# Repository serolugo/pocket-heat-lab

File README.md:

# Pocket Heat Lab

## 📌 Overview
**Pocket Heat Lab** is a compact thermal control laboratory designed to demonstrate and experiment with **digital PID control** on a real physical system.

The project uses an **ESP32** to regulate the temperature of a **BJT transistor used as a thermal plant**, leveraging PWM control, real-time sensing with a thermistor, and external visualization tools for tuning and analysis.

This project was developed with an educational focus, bridging **control theory**, **embedded systems**, and **practical electronics**.

---

## 🔥 System Concept
A BJT transistor, when biased appropriately, dissipates power and generates heat.  
This behavior is exploited as a **slow, inertial thermal plant**, ideal for demonstrating PID control principles.

The ESP32:
- Reads temperature from a 10 kΩ NTC thermistor
- Computes a digital PID controller
- Drives the transistor using a **limited PWM signal**
- Streams data over serial for monitoring and tuning

---

## 🎯 Objectives
- Implement a **digital PID controller** on an ESP32
- Regulate the temperature of a real thermal system
- Explore tuning effects on stability and response
- Provide real-time visualization and interaction
- Maintain safe operating limits for the power device

---

## 🧩 Hardware Overview
- **Microcontroller:** ESP32
- **Thermal plant:** BJT transistor (power dissipation)
- **Temperature sensor:** 10 kΩ NTC thermistor
- **Thermal coupling:** Thermistor mounted with thermal paste
- **PCB:** Custom-designed board

Thermal contact between the sensor and the transistor is critical for accurate control:

---

## ⚡ Safety & Design Constraints
To prevent damage and unsafe operation:
- PWM output to the transistor is **limited to 28 / 255**
- Maximum power dissipation kept below ~2 W
- Sampling and control period set to **100 ms**
- Anti-windup implemented in the integral term

These constraints ensure stable behavior even under poor tuning conditions.

---

## 🧠 Control Algorithm
- **Controller type:** Digital PID
- **Sampling period:** 100 ms
- **Setpoint selection:** Potentiometer (25 °C – 80 °C)
- **Anti-windup:** Integral clamping
- **Output saturation:** PWM constrained

Final stable gains obtained experimentally:
- `Kp = 4`
- `Ki = 0.15`
- `Kd = 2.1`

---

## 📈 Visualization & Tuning
To facilitate tuning and understanding of system behavior, a **Python-based GUI** was implemented using:
- `Tkinter`
- `Matplotlib`
- `PySerial`

Features:
- Real-time plotting of temperature and setpoint
- Live adjustment of PID gains via sliders
- Serial data logging to CSV for offline analysis

---

## 📊 Results
The system demonstrates:
- Stable temperature regulation
- Clear response to setpoint changes
- Expected thermal inertia behavior
- Sensitivity to PID tuning (trial-and-error process)

Example plots of recorded data:

---

## 🖥 PCB Design
The project includes a custom PCB designed specifically for this laboratory setup.

- Rendered PCB view:

- PCB layout:

---

## 🎥 Demo
The following GIF shows the system operating in real time, including temperature response and control action:

---

## 📁 Repository Structure
    pocket-heat-lab/
    ├── firmware/ # ESP32 PID controller code
    ├── software/ # Python visualization and tuning tools
    ├── hardware/ # PCB files
    ├── images/ # Documentation images and GIFs
    ├── docs/
    │ └── CONTROL_TEMPERATURA.pdf
    └── README.md

---

## 🚀 Project Status
✅ Implemented and tested  
✅ Real-time visualization working  
🔧 Open to future improvements (filtering, better sensing, power stage refinement)

---

## 🔮 Possible Improvements
- Signal filtering for temperature measurements
- Dedicated power stage (MOSFET instead of BJT)
- Higher-resolution PWM
- Model-based tuning methods
- Closed-loop current monitoring

---
## 📜 License
MIT License

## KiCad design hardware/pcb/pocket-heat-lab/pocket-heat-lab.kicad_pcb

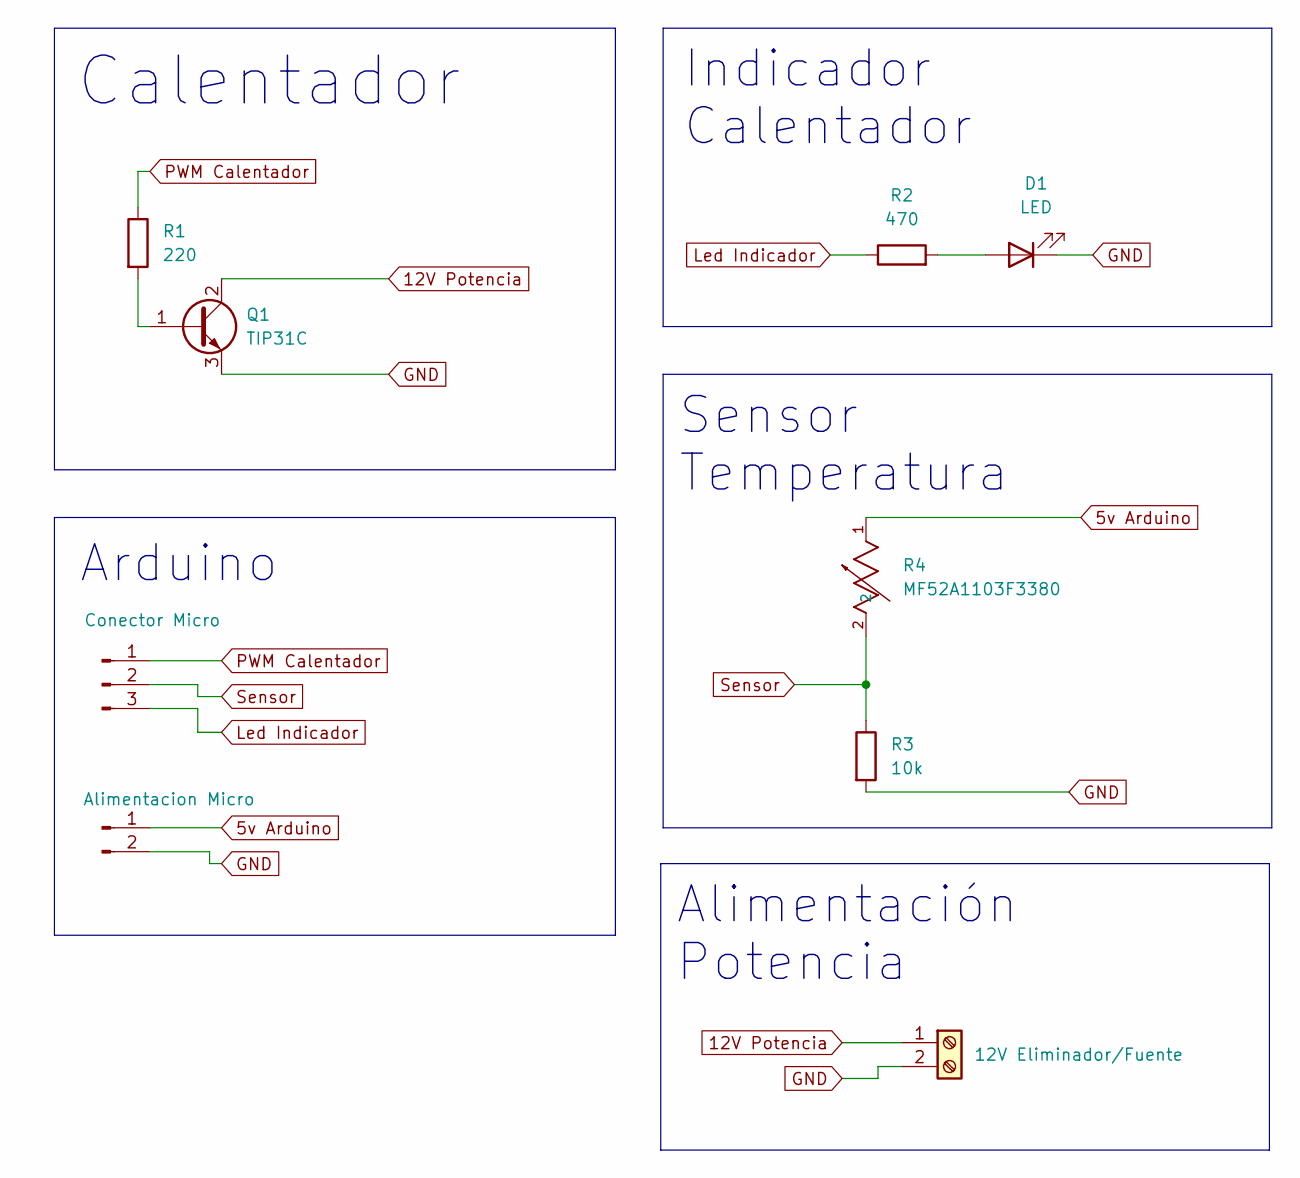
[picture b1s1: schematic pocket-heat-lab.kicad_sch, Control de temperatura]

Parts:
D1: LED; LED_D5.0mm
J1: Conector Micro; PinSocket_1x03_P2.54mm_Vertical
J2: Alimentacion Micro; PinSocket_1x02_P2.54mm_Vertical
J3: 12V Eliminador/Fuente; TerminalBlock_Xinya_XY308-2.54-2P_1x02_P2.54mm_Horizontal
Q1: TIP31C; TO-220-3_Vertical
R1: 220; R_Axial_DIN0309_L9.0mm_D3.2mm_P12.70mm_Horizontal
R2: 470; R_Axial_DIN0309_L9.0mm_D3.2mm_P12.70mm_Horizontal
R3: 10k; R_Axial_DIN0309_L9.0mm_D3.2mm_P12.70mm_Horizontal
R4: MF52A1103F3380; TRES_MF52-A_CTM; MANUFACTURER_PART_NUMBER MF52A1103F3380

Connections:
5v Arduino: J2.1, R4.1
12V Potencia: J3.1, Q1.2 (C)
GND: D1.1 (K), J2.2, J3.2, Q1.3 (E), R3.2
Led Indicador: J1.3, R2.1
unnamed: D1.2 (A), R2.2
unnamed: Q1.1 (B), R1.2
PWM Calentador: J1.1, R1.1
Sensor: J1.2, R3.1, R4.2

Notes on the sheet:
Sensor Temperatura
Alimentación Potencia
Indicador Calentador
Calentador
Arduino

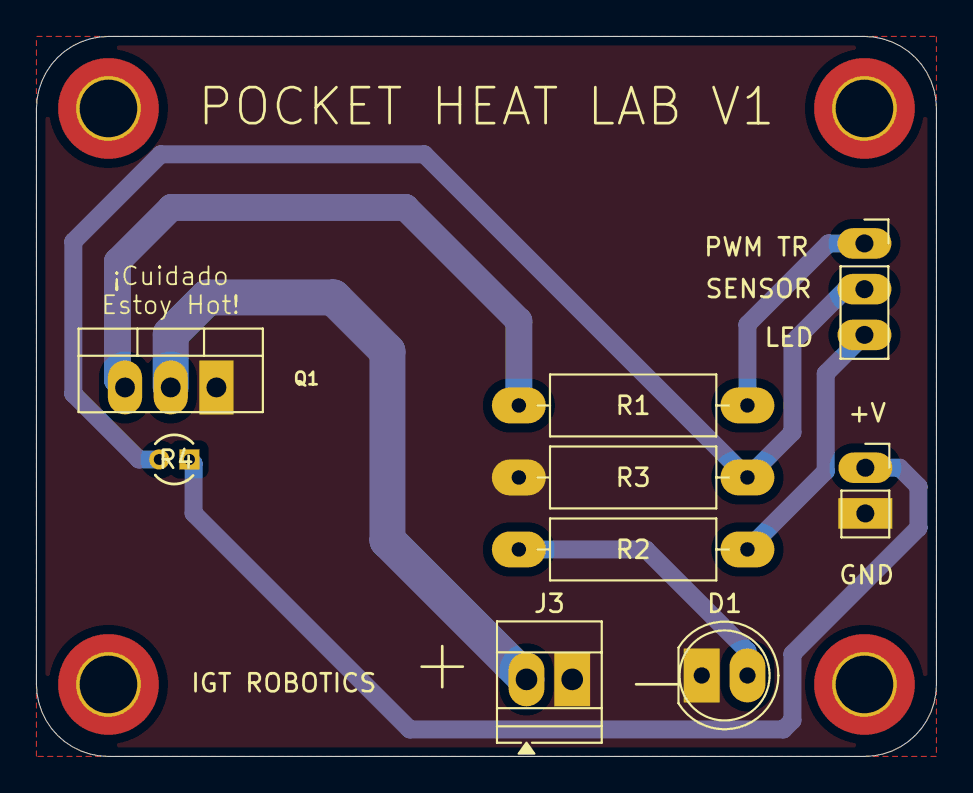
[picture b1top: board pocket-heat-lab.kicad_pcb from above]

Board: 2 copper layers, 50.0 x 40.0 mm, 9 parts (0 on the bottom side), 8 nets.

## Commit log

2026-01-14 files update
2026-01-14 readme update
2026-01-14 Create LICENSE

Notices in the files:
parts and their libraries:
COPYRIGHT: Copyright (C) 2024 Ultra Librarian. All rights reserved.
